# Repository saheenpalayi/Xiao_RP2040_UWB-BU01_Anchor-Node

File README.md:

# Xiao RP2040 UWB-BU01 Anchor-Node!

 The UWB (Ultra wide band ) is a cool thing to have in projects involve indoor location tracking and robotics, tracking devices, Then there is a Module called BU01 DW1000 available for the maker's to explore and add this amazing pice of technology to their project, This documentation of mine is a step to the UWB and the Xiao that I did in Super Fablab Kerala - Koch  

Here is the cool board I made with the Module and Xiao ESP32 C6

## Design of the Board 
I've used Kicad to design the PCB and the Design files and gerber files are included in the repo. I've been following the Makerbase documentation to see the available commercial development board's schematics for the reference and the datasheet of the module all linked bottom of the board. The foot print I've got one of my student Akash at the Fabacademy 2025 who was exploring the Module for his fabacademy final project 
### Schematic

### PCB Layout

### PCB 3D view

## Issues 
 I've faced several issues with the experiment with the new Xiao ESP32 C6 and the module probably the library support I assume

 - The libraries not compiling initially coz its made for older version of Espressif Board
 - the BU01's IRQ pin connected to the Xiao Esp32 C6 is giving an exceptional error on the serial monitor 

 ## Fixes

- Replaced the Xiao ESP32 C6 with the Xiao RP2040 (it was easy since both share same pin footprints)

## References

- [Makerfabs Wiki](https://wiki.makerfabs.com/ESP32_UWB.html) 
- [BU01 Datasheet](https://docs.ai-thinker.com/_media/uwb/docs/bu01_product_specification_en_v1.0.pdf)
- [Getting Started with ESP32 DW1000 UWB (Ultra Wideband) Module](https://how2electronics.com/getting-started-with-esp32-dw1000-uwb-ultra-wideband-module/)
- [Arduino DW1000 Library](https://github.com/thotro/arduino-dw1000/tree/master)

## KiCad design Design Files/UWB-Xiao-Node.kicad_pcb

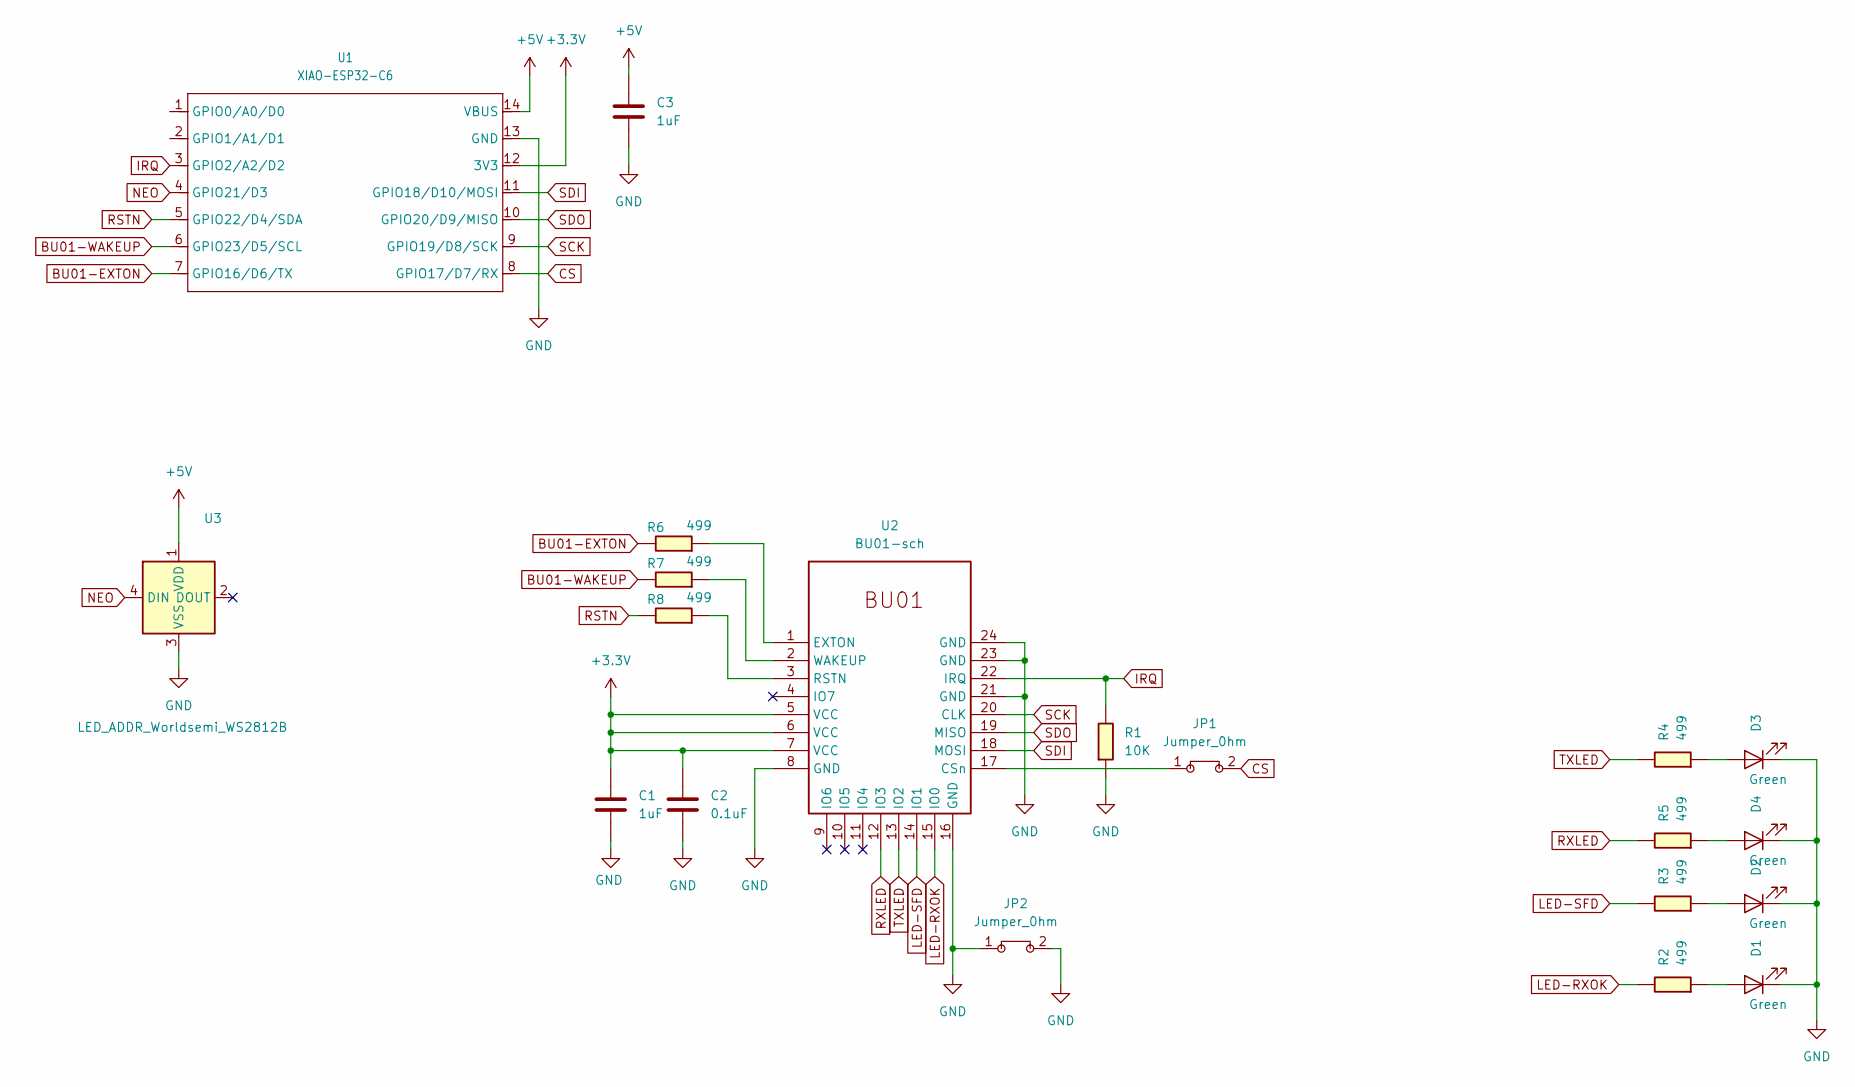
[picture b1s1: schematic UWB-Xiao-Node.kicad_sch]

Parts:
C1, C3: 1uF; C_1206
C2: 0.1uF; C_1206
D1, D2, D3, D4: Green; LED_1206
JP1, JP2: Jumper_0hm; Jumper_1206
R1: 10K; R_1206
R2, R3, R4, R5, R6, R7, R8: 499; R_1206
U1: XIAO-ESP32-C6; XIAO-ESP32C6-SMD
U2: BU01-sch; BU01
U3: LED_ADDR_Worldsemi_WS2812B

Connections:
+3.3V: C1.1, C2.1, U1.12 (3V3), U2.5 (VCC), U2.6 (VCC), U2.7 (VCC)
+5V: C3.1, U1.14 (VBUS), U3.1 (VDD)
BU01-EXTON: R6.1, U1.7 (GPIO16/D6/TX)
BU01-WAKEUP: R7.1, U1.6 (GPIO23/D5/SCL)
CS: JP1.2 (B), U1.8 (GPIO17/D7/RX)
GND: C1.2, C2.2, C3.2, D1.1 (K), D2.1 (K), D3.1 (K), D4.1 (K), JP2.1 (A), JP2.2 (B), R1.2, U1.13 (GND), U2.8 (GND), U2.16 (GND), U2.21 (GND), U2.23 (GND), U2.24 (GND), U3.3 (VSS)
IRQ: R1.1, U1.3 (GPIO2/A2/D2), U2.22 (IRQ)
LED-RXOK: R2.1, U2.15 (IO0)
LED-SFD: R3.1, U2.14 (IO1)
NEO: U1.4 (GPIO21/D3), U3.4 (DIN)
unnamed: D1.2 (A), R2.2
unnamed: D2.2 (A), R3.2
unnamed: D3.2 (A), R4.2
unnamed: D4.2 (A), R5.2
unnamed: JP1.1 (A), U2.17 (CSn)
unnamed: R6.2, U2.1 (EXTON)
unnamed: R8.2, U2.3 (RSTN)
unnamed: R7.2, U2.2 (WAKEUP)
RSTN: R8.1, U1.5 (GPIO22/D4/SDA)
RXLED: R5.1, U2.12 (IO3)
SCK: U1.9 (GPIO19/D8/SCK), U2.20 (CLK)
SDI: U1.11 (GPIO18/D10/MOSI), U2.18 (MOSI)
SDO: U1.10 (GPIO20/D9/MISO), U2.19 (MISO)
TXLED: R4.1, U2.13 (IO2)

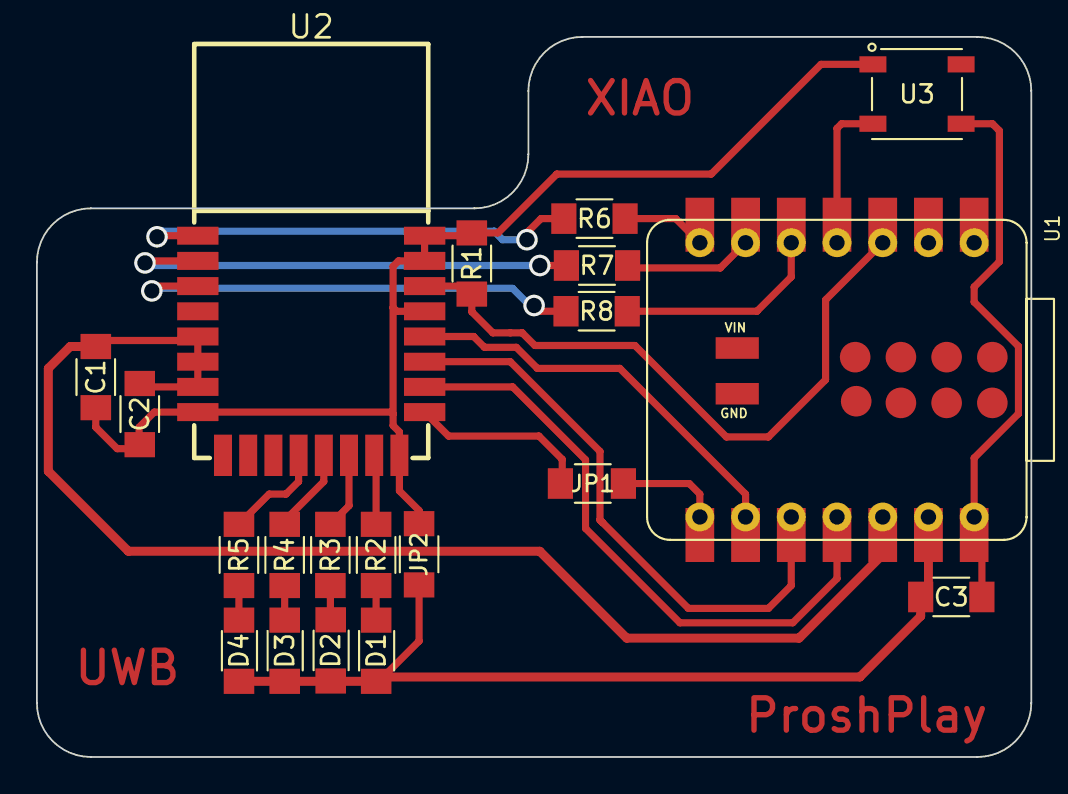
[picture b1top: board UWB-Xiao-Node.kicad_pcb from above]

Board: 2 copper layers, 55.2 x 40.0 mm, 20 parts (0 on the bottom side), 24 nets.

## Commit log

2025-04-09 added initial files
2025-04-09 fixed image link
2025-04-09 added more images
2025-04-09 Updated read me
